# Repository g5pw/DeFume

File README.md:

DeFume
======

A soldering fumes extractor fan controller.

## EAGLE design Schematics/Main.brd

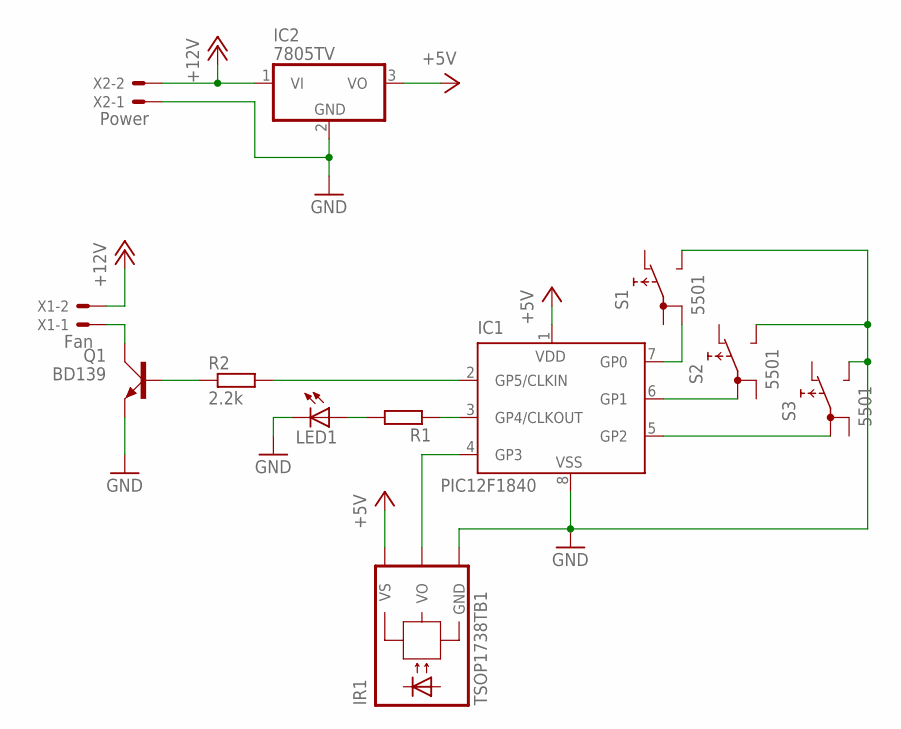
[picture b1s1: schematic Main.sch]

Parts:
IC1: PIC12F1840; DIL8
IC2: 7805TV; TO220V
IR1: TSOP1738TB1; TSOP17_TB1
LED1: LED5MM
Q1: BD139; TO126AV
R1: R-EU_0204/7; 0204/7
R2: 2.2k; 0204/7
S1, S2, S3: 5501
X1: Fan; 22-23-2021
X2: Power; 22-23-2021

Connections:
+5V: IC1.1 (VDD), IC2.3 (VO), IR1.VS
+12V: IC2.1 (VI), X1.2, X2.2
GND: IC1.8 (VSS), IC2.2 (GND), IR1.GND, LED1.K (C), Q1.E, S1.NO, S2.NO, S3.NO, X2.1
unnamed: Q1.B, R2.1
unnamed: IC1.4 (GP3), IR1.VO
unnamed: IC1.5 (GP2), S3.1A
unnamed: IC1.6 (GP1), S2.1A
unnamed: IC1.7 (GP0), S1.1B
unnamed: IC1.2 (GP5/CLKIN), R2.2
unnamed: Q1.C, X1.1
unnamed: IC1.3 (GP4/CLKOUT), R1.1
unnamed: LED1.A, R1.2

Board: 2 copper layers, 12 parts (0 on the bottom side), 12 nets, no tracks yet.

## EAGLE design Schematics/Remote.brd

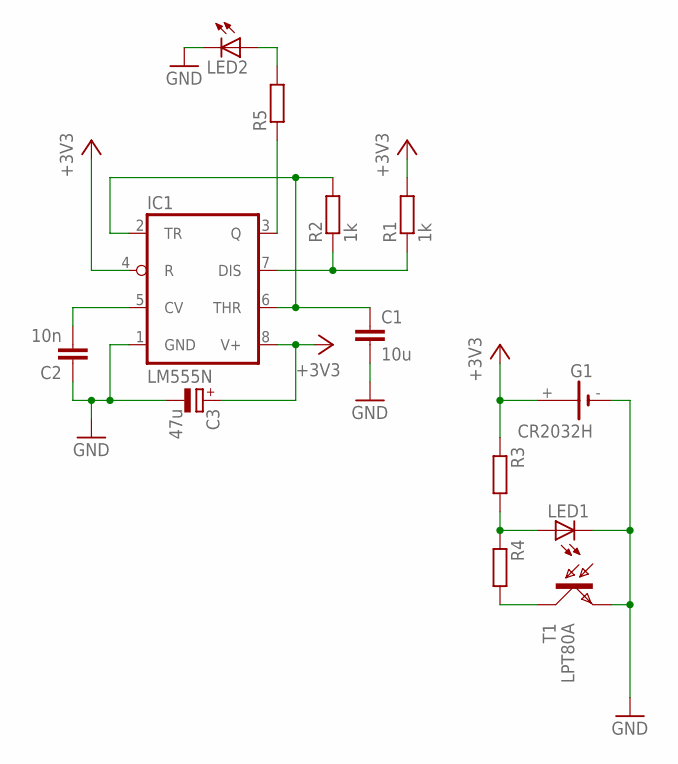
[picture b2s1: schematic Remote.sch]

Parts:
C1: 10u; C025-040X050
C2: 10n; C025-040X050
C3: 47u; E2,5-5
G1: CR2032H
IC1: LM555N; DIL08
LED1, LED2: LED5MM
R1, R2: 1k; 0204/7
R3, R4, R5: R-EU_0204/7; 0204/7
T1: LPT80A

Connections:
+3V3: C3.+, G1.+, IC1.4 (R), IC1.8 (V+), R1.2, R3.1
GND: C1.2, C2.1, C3.-, G1.-, IC1.1 (GND), LED1.K (C), LED2.K (C), T1.E
unnamed: LED1.A, R3.2, R4.1
unnamed: R4.2, T1.C
unnamed: C1.1, IC1.2 (TR), IC1.6 (THR), R2.2
unnamed: IC1.7 (DIS), R1.1, R2.1
unnamed: LED2.A, R5.2
unnamed: IC1.3 (Q), R5.1
unnamed: C2.2, IC1.5 (CV)

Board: 2 copper layers, 13 parts (0 on the bottom side), 9 nets, no tracks yet.

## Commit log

2011-06-10 Initial commit with 12f628
2011-06-10 Added basic PWM
2011-06-10 Deleted unused files
2011-06-10 Simplified PWM controls
2011-06-11 Now uses 2 functions for PWM, removed duty cycle for simplicity (no floating point calculations)
2011-06-15 Reordered code, added flowchart
2011-06-29 Fixed bug: TRISA was getting ORed instead of ANDed
2011-07-02 Added support for buttons, interrupts
2011-07-02 Weak Pullups now working, debugging interrupts Added mTouch datasheet
2011-07-03 Changes to project properties
2011-07-03 PWM button controls now working
2011-07-03 Added TODO, prevented overflows
    Add code to prevent underflows and overflows of the CCPR1L register, commented code better.
2011-07-03 Deleted unused variable, moved some dirs.
    Moved in schematics and created directory for documents. Deleted oldPORTA, unused variable left over by old code.
2011-07-03 Added icon
2011-07-06 Renamed PIC12F1840 datasheet, implemented key repetition: TO BE TESTED prior includind in v0.2
2011-08-11 Restructured code, new version of mplabX
2011-08-11 Added project for remote, alignment adjustments
2011-08-11 Added board for remote, added IR decoder to main schematic
2011-08-19 Renamed to DeFume
    Added some minor changes in the schematics and added project description in Eagle
2011-10-27 Idea changed
    Remote bill not be a microcontroller, but just a 555 timer.
2011-11-10 Upgraded to beta eagle version - Now remote uses just a 555 timer and not a microrontroller
2011-11-10 Revert "Upgraded to beta eagle version - Now remote uses just a 555 timer and not a microrontroller"
    This reverts commit 387f62994e57266958dc42b57172b24771972b22.
2011-11-10 Revert 387f62994e57266958dc42b57172b24771972b22^..HEAD
2011-11-11 Upgraded to beta eagle version - Now remote uses just a 555 timer and not a microrontroller
    This should fix this mess.
2011-11-11 All working now
    Issues with repo resolved, back to normal!
2012-05-15 Added README
2012-05-15 Removed datasheets
2012-05-15 Ported schematics to next version of EAGLE
2013-04-04 Add license
